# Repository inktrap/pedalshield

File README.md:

# Pedalshield Due

I wanted "my own" overview of pedalshield resources, one that allows for collaboration and forks, and that is always available. So here we go.

## General

 - [electrosmash site](https://www.electrosmash.com/pedalshield)
 - the [most important topics](https://www.electrosmash.com/forum/software-pedalshield/233-best-pedalshield-due-topics) from the [electrosmash due forum](https://www.electrosmash.com/forum/pedalshield-due)
 - [howtos](https://www.electrosmash.com/forum/hardware-pedalshield/20-how-to-build-pedalshield-in-5-steps?lang=en)  ([pdf](https://www.electrosmash.com/media/kunena/attachments/44/How-to-Build-pedalSHIELD-DUE.pdf), [flickr](https://www.flickr.com/photos/electrosmash/sets/72157638250771595/), [youtube](
https://www.youtube.com/watch?v=0nAO9C56jZM))

## Hardware

Analysis

 - [hardware analysis](https://www.electrosmash.com/forum/hardware-pedalshield/166-hardware-analysis-of-pedalshield)
 - [circuit diagram](https://i.stack.imgur.com/7KS3T.png) → `circuit.png`
 - [input/output stages](https://www.electrosmash.com/forum/hardware-pedalshield/73-input-output-stages)

Parts

 - [BOM](https://www.electrosmash.com/media/kunena/attachments/44/BOM-pedalSHIELD.rar) (rar) `BOM-pedalSHIELD.rar` → `bom` and [alternatives](https://www.electrosmash.com/forum/hardware-pedalshield/17-pedalshield-bill-of-materials-and-alternatives)
 - [best options to power arduino due](http://www.electrosmash.com/forum/hardware-pedalshield/26-powering-arduino-due?lang=en)
 - [troubleshooting guide](http://www.electrosmash.com/forum/hardware-pedalshield/72-guide-to-troubleshoot-pedalshield?lang=en)

Files

 - [kicad schematics](https://www.electrosmash.com/forum/hardware-pedalshield/18-kicad-schematics-pedalshield) via `PedalShield-rev.E-nativefiles.zip` → `kicad`
 - [gerber files](https://www.electrosmash.com/media/kunena/attachments/631/pedalSHIELDGerberFIles.rar) (rar) `pedalSHIELDGerberFIles.rar` → `gerber`
 - [pcb transfers](http://www.electrosmash.com/forum/hardware-pedalshield/82-pedalshield-pcb-transfers?lang=en)

## Software

 - [how to program pedalshield](http://www.electrosmash.com/forum/software-pedalshield/21-how-to-start-programming-pedalshield?lang=en)
 - effects: [bitcrusher](http://www.electrosmash.com/forum/software-pedalshield/156-bitcrusher-sample-rate-reducer-with-lfo?lang=en#592), [schroeder's reverb](http://www.electrosmash.com/forum/software-pedalshield/175-schoreder-s-reverb?lang=en), [Chorus, Chorus Dattorro, Echo, Flanger, Vibrato, Fuzz, Reverb Schroeder, Tremolo](http://www.electrosmash.com/forum/software-pedalshield/133-several-codes-based-on-pedalshield-library?lang=en#481) all by AndrewHPAvei
 - [all pedals](https://www.open-electronics.org/wp-content/uploads/2014/04/pedalSHIELD-all-pedals.rar) (rar) `pedalSHIELD-all-pedals.rar` → `pedals`

## Misc

 - [covers and cases on thingiverse](https://www.thingiverse.com/search?q=pedalshield&sa=&dwh=485aa2707f64633&type=things&sort=relevant), [printed cover](https://www.thingiverse.com/thing:210541) → `covers`. Laser cut covers are in the electrosmash shop as part of the kit.
 - [op amp book](http://www.ee.nmt.edu/~anders/courses/ee322s10/op-amp-slod006a.pdf) (pdf) `op-amp-slod006a.pdf`
 - connect a [screen](http://www.electrosmash.com/forum/hardware-pedalshield/94-mounting-an-oled-screen-on-my-pedalshield?lang=en), a [microphone](http://www.electrosmash.com/forum/hardware-pedalshield/39-connecting-a-microphone-to-pedalshield?lang=en), … also mods for a [bass guitar](http://www.electrosmash.com/forum/hardware-pedalshield/79-guitar-pedal-modification-pedalshield-for-bass?lang=en) … these are just copied from the [important topics](https://www.electrosmash.com/forum/software-pedalshield/233-best-pedalshield-due-topics) linked at the beginning.

# License

Published under the [Attribution-NonCommercial 3.0 Unported (CC BY-NC 3.0)](https://creativecommons.org/licenses/by-nc/3.0/) license. Some 
[rights are reserved](https://www.electrosmash.com/rights). Currently all of this can be found through [the links mentioned here](https://www.electrosmash.com/pedalshield) anyways.

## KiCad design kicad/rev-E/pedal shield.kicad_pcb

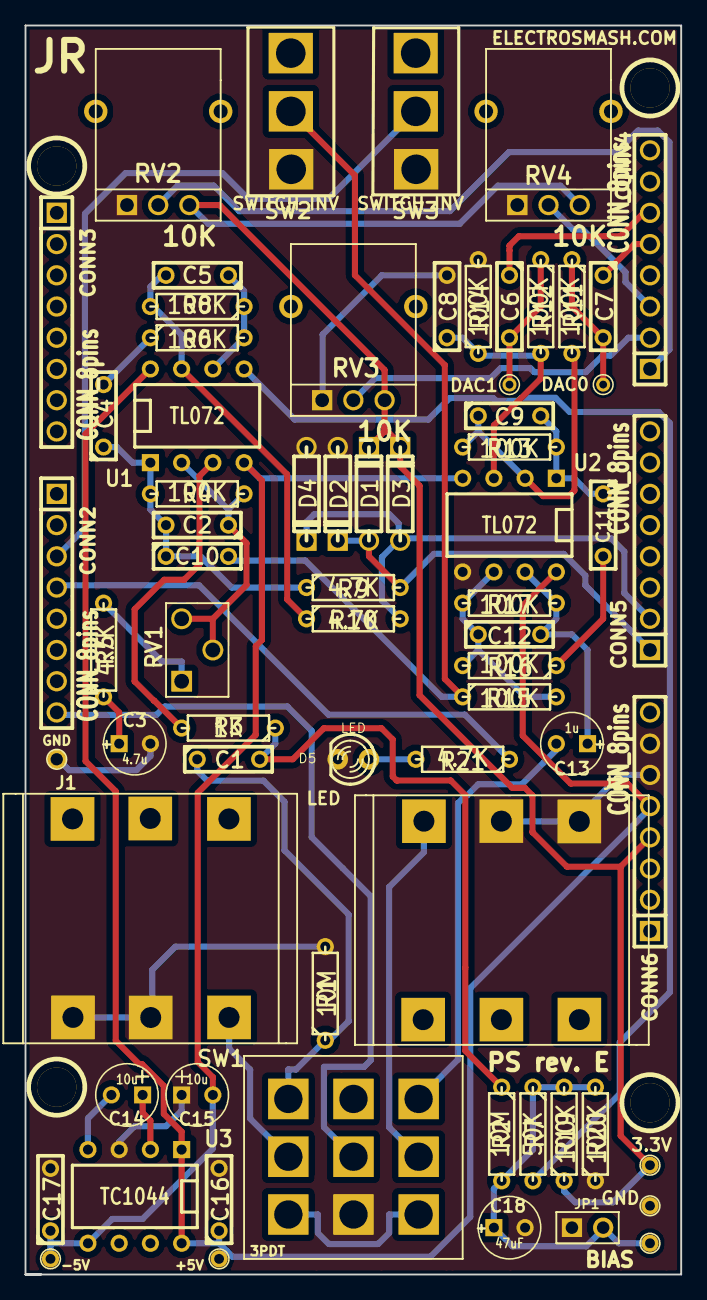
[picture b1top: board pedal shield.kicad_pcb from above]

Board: 2 copper layers, 53.3 x 101.6 mm, 73 parts (0 on the bottom side), 42 nets.

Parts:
C1, C4, C6, C7, C10, C11: 0.1u; C2
C2, C5, C8, C9, C12: 47p; C2
C3: 4.7u; C1V5
C13: 1u; C1V5
C14, C15: 10u; C1V5
C16, C17: 100n; C2
C18: 47uF; C1V5
CONN2, CONN3, CONN4, CONN5, CONN6: CONN_8pins; SIL-8
D1, D2, D3, D4: 1N5817; D3
D5: LED; LED-3MM
J1: Guitar_IN; JACK_AUDIO
J2: OUTPUT; JACK_AUDIO
JP1: JUMPER; PIN_ARRAY_2X1
R1, R2: 10M; R3
R3: 1K; R3
R4, R6, R8, R11, R12, R13, R14, R15, R16, R17, R19, R20: 100K; R3
R5, R9, R10, R21: 4.7K; R3
R7: 50K; R3
RV1: 500K; PIN_ARRAY_3X1
RV2, RV3, RV4: 10K; RVAR
SW1: SWITCH_3PDT; 3PDT
SW2: SWITCH_INV; SW_SPDT_pedalSHIELD
SW3: SWITCH_INV; SW_SPDT
TP1: 3V3 TP; PINTST
TP2: 1V6 TP; PINTST
TP3, TP6: GND TP; PINTST
TP4: +5V TP; PINTST
TP5: -5V TP; PINTST
TP7: DAC0; PINTST
TP8: DAC1; PINTST
U1, U2: TL072; DIP-8__300
U3: TC1044; DIP-8__300
hole1: hole1; 1pin
hole2, hole3, hole4: P***; 1pin

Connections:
+3.3V: CONN6.4, D1.2, D3.2, R19.1, RV2.3, RV3.3, RV4.3, TP1.1
+5V: C16.1, CONN6.5, TP4.1, U1.8, U2.8, U3.1, U3.8
-5V: C15.1, C17.1, TP5.1, U1.4, U2.4, U3.5
/AD0: CONN5.1, D1.1, D2.2, R9.2
/AD1: CONN5.2, D3.1, D4.2, R10.2
/AD8: CONN4.1, RV2.2
/AD9: CONN4.2, RV3.2
/AD10: CONN4.3, RV4.2
/Bypass: SW1.3, SW1.9
/DAC0: C7.1, CONN4.5
/DAC1: C6.1, CONN4.6
/FX In: C1.1, R1.1, SW1.1
/FX Out: C13.2, SW1.7
/IN_BUFFERED: C2.2, C4.1, C10.1, R4.2, R9.1, U1.1
/Input Jack: J1.1, SW1.2
/Output JAck: J2.1, SW1.8
/PWM2: CONN2.3, SW3.2
/PWM3: CONN2.4, R21.1
/PWM7: CONN2.8, SW1.5
GND: C3.2, C8.2, C15.2, C16.2, C17.2, C18.2, CONN6.6, CONN6.7, D2.1, D4.1, D5.2, J1.2, J1.3, J2.2, J2.3, JP1.1, R1.2, R14.2, R20.1, RV2.1, RV3.1, RV4.1, SW1.6, SW2.1, SW3.1, TP3.1, TP6.1, U2.5, U3.3
unnamed: D5.1, R21.2
unnamed: C18.1, JP1.2, R2.2, R7.1, R19.2, R20.2, TP2.1
unnamed: C2.1, R4.1, RV1.2, RV1.3, U1.2
unnamed: C3.1, R5.1
unnamed: R5.2, RV1.1
unnamed: C9.2, C11.1, R13.2, U2.1
unnamed: C12.2, C13.1, R17.2, U2.7
unnamed: C11.2, R16.1
unnamed: C8.1, R12.2, R14.1, U2.3
unnamed: C12.1, R15.2, R16.2, R17.1, U2.6
unnamed: C14.2, U3.4
unnamed: C14.1, U3.2
unnamed: R7.2, U1.5
unnamed: C10.2, R15.1, SW2.2
unnamed: C7.2, R11.1, TP7.1
unnamed: C6.2, R12.1, TP8.1
unnamed: C5.2, R8.2, R10.1, U1.7
unnamed: C5.1, R6.2, R8.1, U1.6
unnamed: C4.2, R6.1
unnamed: R3.2, U1.3
unnamed: C1.2, R2.1, R3.1
unnamed: C9.1, R11.2, R13.1, U2.2

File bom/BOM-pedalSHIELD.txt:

pedalSHIELD Bill of Materials / Part List.
 
Value		Qty		References					Description					Mouser Reference
Capacitors	 	 	 	 
270p		5		C2 C5 C8 C9 C12					Ceramic Disc Cap.				140-50S5-271J-RC
0.1u		6		C1 C4 C6 C7 C10 C11				Film Capacitors.				ECQ-V1H104JL
1u		1		C13						Aluminium Electrolytic Capacitors 		ECE-A1HKA010
4.7u		1		C3						Aluminium Electrolytic Capacitors 		ECE-A1EKA4R7
10u		2		C14 C15						Aluminium Electrolytic Capacitors 		ECE-A1HKA100B
47uF		1		C18						Aluminium Electrolytic Capacitors 		REA470M1CBK-0511P
Resistors	 	 	 
1K		2		R3 R21						Metal Film Resistors, 1% Tol.			MF1/4DC1001F
4.7K		3		R5 R9 R10 					Metal Film Resistors, 1% Tol.			MF1/4DCT52R4701F
50K		1		R7						Metal Film Resistors, 1% Tol.			MF1/4DCT52R4992F
100K		12		R4 R6 R8 R11 R12 R13 R14 R15 R16 R17 R19 R20	Metal Film Resistors, 1% Tol.			MF1/4DCT52R1003F
10M		2		R1 R2						Metal Film Resistors, 1% Tol.			RK1/4DC1005F
500K		1		RV1						Trimmer Resistors - 9mm Single Turn		3319W-3-504
10K		3		RV2 RV3 RV4					Alpha Potentiometers Flat 20mm			RK09L114001T
Knobs		3		RV2, RV3, RV4					Plastic Knob with screw, Shaft:6.35mm		450-2023-GRX
Others	 	 	 	 
1N5817		4		D1 D2 D3 D4					Schottky Diodes Vr/20V Io/1A 			1N5817
LED		1		D5						Through hole, blue led.				C4SMG-BJS-CQ0T0451
SWITCH_3PDT	1		SW1						3PDT True Bypass Footswitch 			107-SF17020F-32-21RL
SWITCH_INV	2		SW2 SW3						Toggle Switch SPDT				612-100-A1111
Connectors	 	 	 	 
CONN_8pins	5		CONN2 CONN3 CONN4 CONN5 CONN6  			40pins stripe 
JACKS		2		JI, J2						Neutrix 1/4 stereo Chrome Phone Conn.		NMJ6HCD2
IC's	 	 	 	 
TL072		2		U1 U2						Operational amplifier.				TL072IPE4
TC1044		1		U3						Voltage switching regulator. 			TC1044SCPA
8PINSOCKETS	3		U1, U2, U3					8pin DIP plastic socket.			1-390261-2
Mechanic	 	 	 	 
pedalSHIELD PCB	1								Dual Layer 2x4 PCB with soldermask.	 
Plastic Cover	1								3D printed plastic cover protector.

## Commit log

2022-08-15 init
2022-08-15 add licensing info
2022-08-16 add links from pedalboard summary topic
2022-08-16 restructure links
